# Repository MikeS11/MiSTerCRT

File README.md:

[![Contributors][contributors-shield]][contributors-url]
[![Forks][forks-shield]][forks-url]
[![Stargazers][stars-shield]][stars-url]
[![Issues][issues-shield]][issues-url]
[![MIT License][license-shield]][license-url]
[![Twitter][Twitter-shield]][Twitter-url]

<!-- PROJECT LOGO -->
<br />
<p align="center">
  
  <a href="https://github.com/MikeS11/MiSTerCRT">
   <br> 
  </a>
  <h3 align="center">MiSTerCRT - S-Video / Composite Adapter</h3>

  <p align="center">

<!-- TABLE OF CONTENTS -->
## Table of Contents

* [About the Project](#about-the-project)
  * [Built With](#Build-Requirements)
* [Getting Started](#getting-started)
  * [Prerequisites](#prerequisites)
* [License](#license)
* [Contact](#contact)
* [Acknowledgements](#acknowledgements)

<!-- ABOUT THE PROJECT -->
## About The Project
Wanted to add a open source option for getting S-Video / Composite out of a MiSTer and add some flexiblity to tune the NTSC crystal through a trim capacitor.
  
#Note - I still need to test out the composite port

### Getting Started
You can use either power from the 5V VGA port (Through the IO Board jumper) or directly through USB. Make sure you only use one of those options.

Also I've added a trim capacitor to tune the NTSC crystal if required. (I've noticed some cores tend to have some additional flicker that can be tuned to improve the image through a trim capacitor.
  
For settings in the ini file, make sure vga_scaler is off and you flip sync on green on the IO board to off as well. 

### Build Requirements:
  
|QUANTITY |	PART NUMBER	|	DESCRIPTION	| UNIT PRICE (Canadian)	|
|  ------------- | ------------- | ------------- | ------------- |
| 1		 |     CP-2240-ND		|	CONN RCPT FMALE MINI DIN 4P SLDR	|  2.38000		|
| 1		 |     CP-1421-ND		|	CONN RCA JACK MONO 3.2MM R/A		  |  2.16000		|
| 1		 |     XC584CT-ND		|	CRYSTAL 3.579545MHZ 17PF SMD		  |  2.47000		|
| 1		 |     AD724JRZ-ND		|	IC ENCODER RGB TO NTSC 16-SOIC		|  26.77000	|
|1	|	609-10033526-N3222MLFCT-ND	|MINI USB B TYPE RECEPT	|		1.09000		|
|1	|	1727-3776-ND	|		IC INVERTER 6CH 6-INP 14SO	|	0.51400	|
|1 | 	311-1.00KCRCT-ND| 		RES SMD 1K OHM 1% 1/8W 0805 | 0.02340			| 
| 6	|	RMCF0805FT75R0CT-ND		|RES 75 OHM 1% 1/8W 0805		|	0.01540		|  
|2 | 311-10.0KCRCT-ND| 	RES SMD 10K OHM 1% 1/8W 0805 | 0.02340	|
|1	|	13-RC2512FK-071MLCT-ND	|	RES SMD 1M OHM 1% 1W 2512	|	0.47300		|
|5 | 399-1171-1-ND	| CAP CER 0.1UF 50V X7R 0805 | 0.11020	|
|2 | 399-15693-1-ND| 		CAP CER 10UF 10V X7R 0805 | 0.85900		|  
|1	|	311-4241-1-ND		|	CAP CER 62PF 50V NPO 0805	(60PF is recommended if you can find it)|0.14200		|
|1	|	720-VJ0805A470GXJPW1BCCT-ND	|CAP CER 47PF 16V C0G/NP0 0805	|	0.22600		|   
|3	|	399-9744-1-ND		|	CAP TANT 220UF 20% 10V 2917	|	1.90000		|  
| 1		 |     SG9212-ND		|	  Optional - CAP TRIMMER 5-25PF 25V SMD (Recommended to fine tune NTSC signal)   |   1.40000	|
| 1		 |   XM4L-1542-132  | CONN D-SUB HD RCPT 15P R/A SLDR  | 4.47000 | 

If you need jumpers, S9001-ND, CONN JUMPER SHORTING GOLD FLASH

  <a href="https://github.com/MikeS11/MiSTerCRT">
   <br> 
  </a>

<!-- CONTRIBUTING -->
## Contributing

Contributions are what make the open source community such an amazing place to be learn, inspire, and create. Any contributions you make are **greatly appreciated**.

1. Fork the Project
2. Create your Feature Branch (`git checkout -b feature/AmazingFeature`)
3. Commit your Changes (`git commit -m 'Add some AmazingFeature'`)
4. Push to the Branch (`git push origin feature/AmazingFeature`)
5. Open a Pull Request

<!-- LICENSE -->
## License

Distributed under the MIT License. See `LICENSE` for more information.

<!-- CONTACT -->
## Contact

Mike Simone - [@mikesimone3](https://twitter.com/mikesimone3) 

Project Link: [https://github.com/MikeS11/MiSTerCRT](https://github.com/MikeS11/MiSTerCRT)

<!-- ACKNOWLEDGEMENTS -->
## Acknowledgements

<!-- MARKDOWN LINKS & IMAGES -->
<!-- https://www.markdownguide.org/basic-syntax/#reference-style-links -->
[contributors-shield]: https://img.shields.io/github/contributors/MikeS11/MiSTerCRT.svg?style=flat-square
[contributors-url]: https://github.com/MikeS11/MiSTerCRT/graphs/contributors
[forks-shield]: https://img.shields.io/github/forks/MikeS11/MiSTerCRT.svg?style=flat-square
[forks-url]: https://github.com/MikeS11/MiSTerCRT/network/members
[stars-shield]: https://img.shields.io/github/stars/MikeS11/MiSTerCRT.svg?style=flat-square
[stars-url]: https://github.com/MikeS11/MiSTerCRT/stargazers
[issues-shield]: https://img.shields.io/github/issues/MikeS11/MiSTerCRT.svg?style=flat-square
[issues-url]: https://github.com/MikeS11/MiSTerCRT/issues
[license-shield]: https://img.shields.io/github/license/MikeS11/MiSTerCRT.svg?style=flat-square
[license-url]: https://github.com/MikeS11/MiSTerCRT/blob/master/LICENSE.txt
[twitter-shield]: https://img.shields.io/badge/-Twitter-black.svg?style=flat-square&logo=Twitter&colorB=555
[twitter-url]: https://Twitter.com/mikesimone3
[product-screenshot]: images/screenshot.png

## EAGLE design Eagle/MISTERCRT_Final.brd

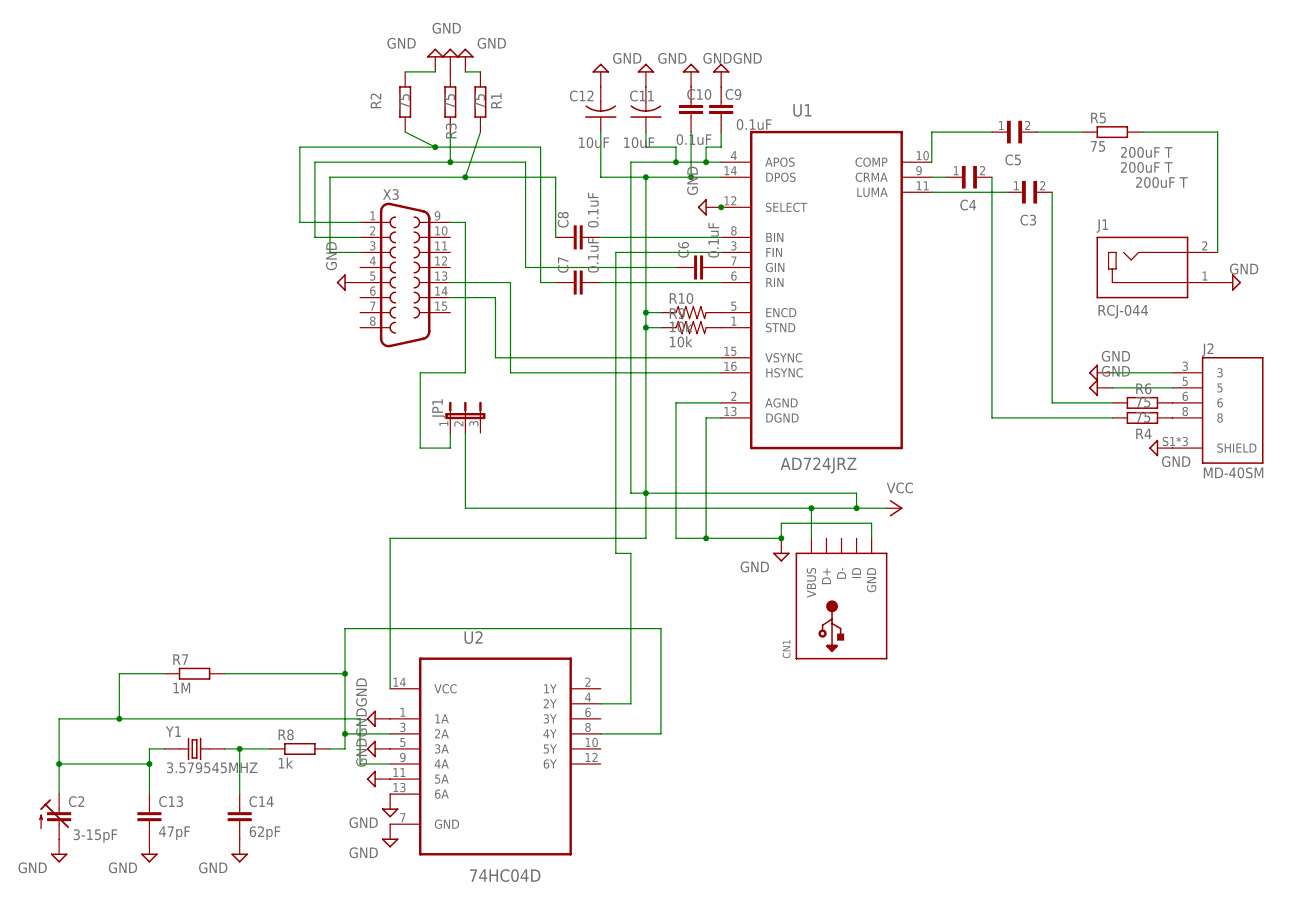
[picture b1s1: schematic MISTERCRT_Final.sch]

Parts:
C2: 3-15pF; CTRIM3018_11
C3, C4, C5: 200uF T; CAPMP7343X430N
C6, C7, C8, C9, C10: 0.1uF; C0805
C11, C12: 10uF; C1206K
C13: 47pF; C0805
C14: 62pF; C0805
CN1: USBMINIB; USB-MINIB
J1: RCJ-044; CUI_RCJ-044
J2: MD-40SM; CUI_MD-40SM
JP1: JP2W
R1, R2, R3, R4, R5, R6: 75; M0805
R7: 1M; R2512
R8: 1k; R0805
R9, R10: 10k; R0805
U1: AD724JRZ; SOIC127P1032X265-16N
U2: 74HC04D; SOIC127P600X175-14N
X3: F15HDH; HDF15H
Y1: 3.579545MHZ; XTAL_ECS-35-17-18-TR

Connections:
GND: C2.- (A), C9.2, C10.2, C11.2, C12.2, C13.2, C14.2, CN1.GND, J1.1, J2.3, J2.5, J2.S1 (SHIELD), J2.S2 (SHIELD), J2.S3 (SHIELD), R1.2, R2.2, R3.2, U1.2 (AGND), U1.12 (SELECT), U1.13 (DGND), U2.1 (1A), U2.5 (3A), U2.7 (GND), U2.11 (5A), U2.13 (6A), X3.5
unnamed: C2.+ (E), C13.1, R7.1, U2.9 (4A), Y1.1, Y1.4 (1)
unnamed: R10.2, U1.5 (ENCD)
unnamed: U1.3 (FIN), U2.4 (2Y)
unnamed: C7.1, R2.1, X3.1
unnamed: C6.1, R3.1, X3.2
unnamed: C8.1, R1.1, X3.3
unnamed: U1.16 (HSYNC), X3.13
unnamed: U1.15 (VSYNC), X3.14
unnamed: J2.6, R6.2
unnamed: J2.8, R4.2
unnamed: C3.2, R6.1
unnamed: C3.1, U1.11 (LUMA)
unnamed: C4.2, R4.1
unnamed: C4.1, U1.9 (CRMA)
unnamed: C5.1, U1.10 (COMP)
unnamed: C5.2, R5.1
unnamed: J1.2, R5.2
unnamed: JP1.1, X3.9
unnamed: C6.2, U1.7 (GIN)
unnamed: C7.2, U1.6 (RIN)
unnamed: C8.2, U1.8 (BIN)
unnamed: C14.1, R8.1, Y1.2, Y1.3 (2)
unnamed: R7.2, R8.2, U2.3 (2A), U2.8 (4Y)
unnamed: R9.2, U1.1 (STND)
VCC: C9.1, C10.1, C11.1, C12.1, CN1.VBUS, JP1.2, R9.1, R10.1, U1.4 (APOS), U1.14 (DPOS), U2.14 (VCC)

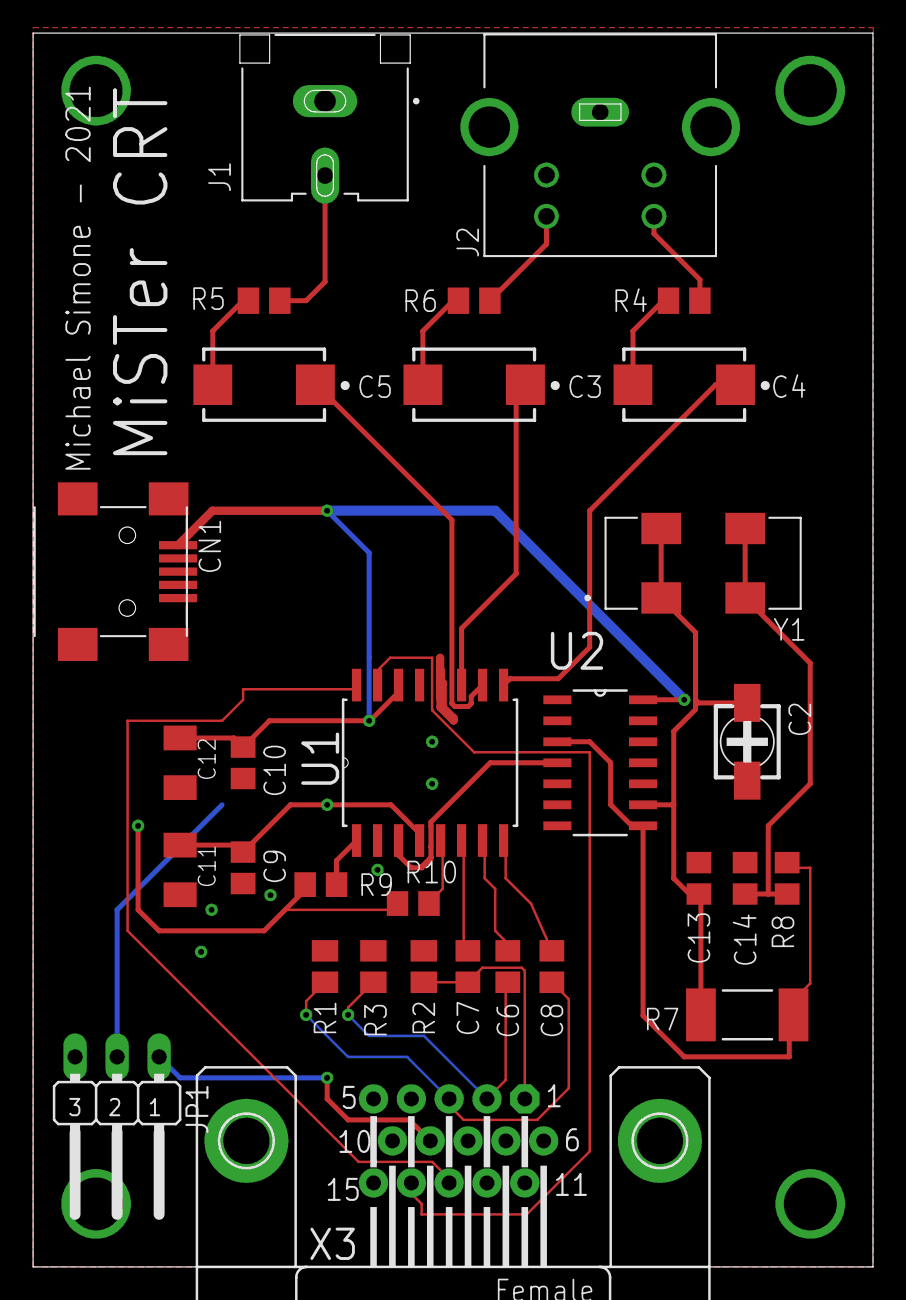
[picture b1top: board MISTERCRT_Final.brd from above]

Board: 2 copper layers, 50.8 x 74.6 mm, 31 parts (0 on the bottom side), 26 nets.

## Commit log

2021-07-05 MiSTerCRT - RGB to S-Video / Composite Adapter
    MiSTerCRT - RGB to S-Video / Composite Adapter
2021-07-06 Add Digikey BOM
    Quick Note: A few items are out of stock and one is out of production, but users could just find a suitable replacement with the tools on Digikey easily enough. Figured I'd start with your list thoug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
2021-07-07 Added Case Model
    Added Case Model
